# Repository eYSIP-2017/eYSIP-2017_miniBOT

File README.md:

# eYSIP-2017_miniBOT
A miniBot is designed and developed. Add necessary functions in Firebird-Blockly

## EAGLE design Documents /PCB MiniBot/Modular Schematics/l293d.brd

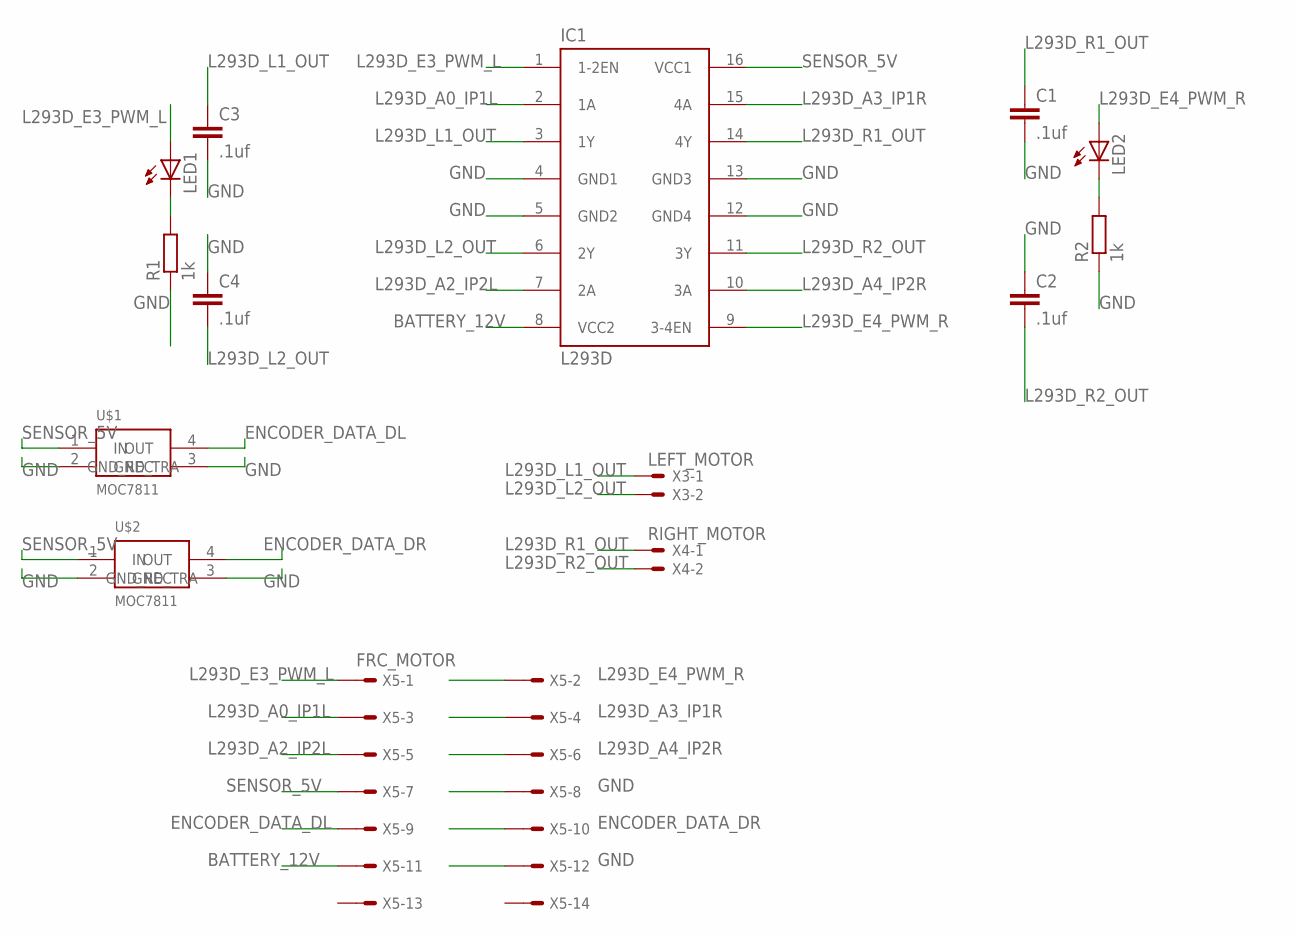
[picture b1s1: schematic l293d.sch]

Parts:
C1, C2, C3, C4: .1uf; C1206
IC1: L293D; DIL16
LED1, LED2: LEDSMT1206; 1206
R1, R2: 1k; M1206
U$1, U$2: MOC7811; THROUGH_HOLE_NORMAL
X3: LEFT_MOTOR; 22-23-2021
X4: RIGHT_MOTOR; 22-23-2021
X5: FRC_MOTOR; 057-014-1

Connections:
BATTERY_12V: IC1.8 (VCC2), X5.11
ENCODER_DATA_DL: U$1.4 (OUT), X5.9
ENCODER_DATA_DR: U$2.4 (OUT), X5.10
GND: C1.2, C2.1, C3.2, C4.1, IC1.4 (GND1), IC1.5 (GND2), IC1.12 (GND4), IC1.13 (GND3), R1.1, R2.1, U$1.2 (GND_TRA), U$1.3 (GND_REC), U$2.2 (GND_TRA), U$2.3 (GND_REC), X5.8, X5.12
L293D_A0_IP1L: IC1.2 (1A), X5.3
L293D_A2_IP2L: IC1.7 (2A), X5.5
L293D_A3_IP1R: IC1.15 (4A), X5.4
L293D_A4_IP2R: IC1.10 (3A), X5.6
L293D_E3_PWM_L: IC1.1 (1-2EN), LED1.A, X5.1
L293D_E4_PWM_R: IC1.9 (3-4EN), LED2.A, X5.2
L293D_L1_OUT: C3.1, IC1.3 (1Y), X3.1
L293D_L2_OUT: C4.2, IC1.6 (2Y), X3.2
L293D_R1_OUT: C1.1, IC1.14 (4Y), X4.1
L293D_R2_OUT: C2.2, IC1.11 (3Y), X4.2
unnamed: LED1.C, R1.2
unnamed: LED2.C, R2.2
SENSOR_5V: IC1.16 (VCC1), U$1.1 (IN), U$2.1 (IN), X5.7

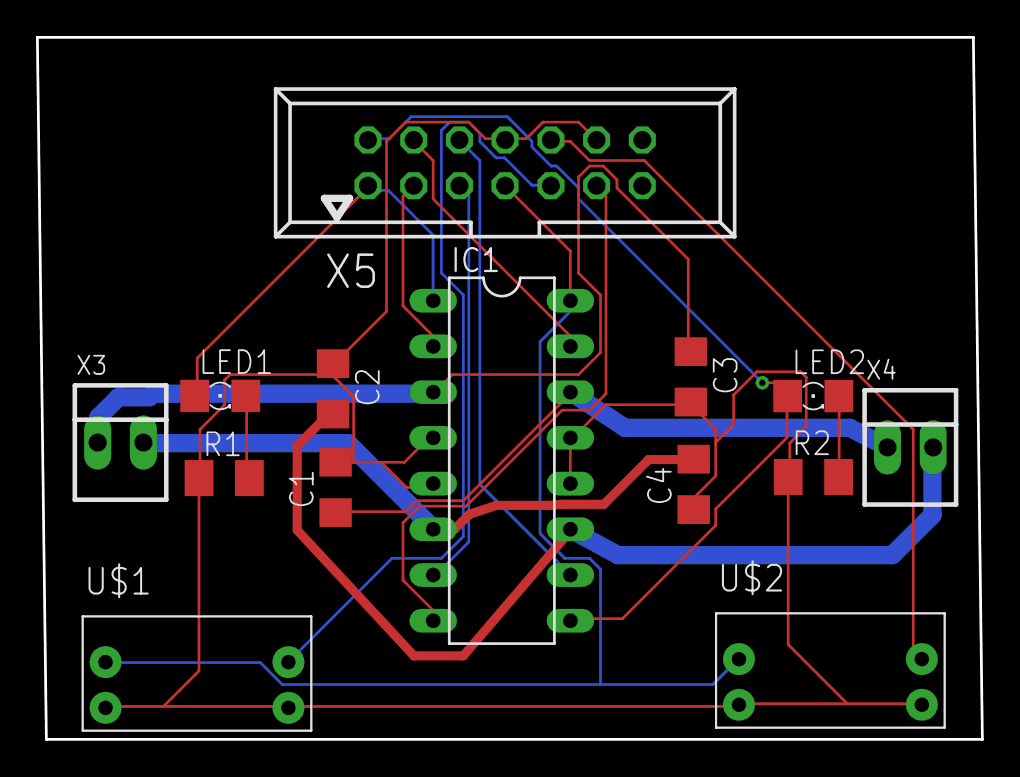
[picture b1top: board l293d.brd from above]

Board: 2 copper layers, 52.5 x 39.0 mm, 14 parts (0 on the bottom side), 17 nets.

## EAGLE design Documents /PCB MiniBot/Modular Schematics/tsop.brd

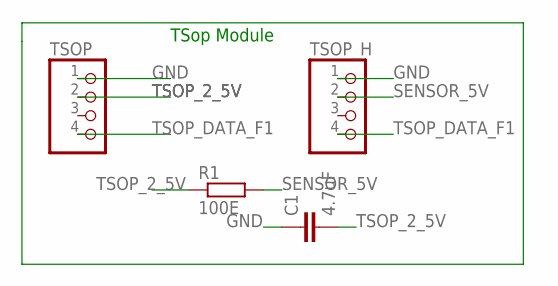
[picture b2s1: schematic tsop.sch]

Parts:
C1: 4.7uF; C1206
R1: 100E; R1206
TSOP: PINHD-1X4; 1X04
TSOP_H: PINHD-1X4; 1X04

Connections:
GND: C1.1, TSOP.1, TSOP_H.1
SENSOR_5V: R1.2, TSOP_H.2
TSOP_2_5V: C1.2, R1.1, TSOP.2
TSOP_DATA_F1: TSOP.4, TSOP_H.4

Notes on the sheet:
TSop Module

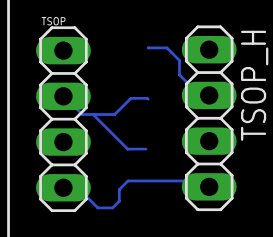
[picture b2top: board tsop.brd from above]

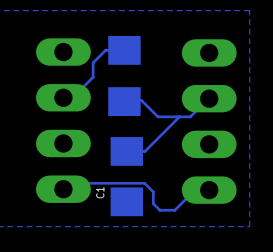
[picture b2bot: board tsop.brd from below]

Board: 2 copper layers, 4 parts (2 on the bottom side), 4 nets.

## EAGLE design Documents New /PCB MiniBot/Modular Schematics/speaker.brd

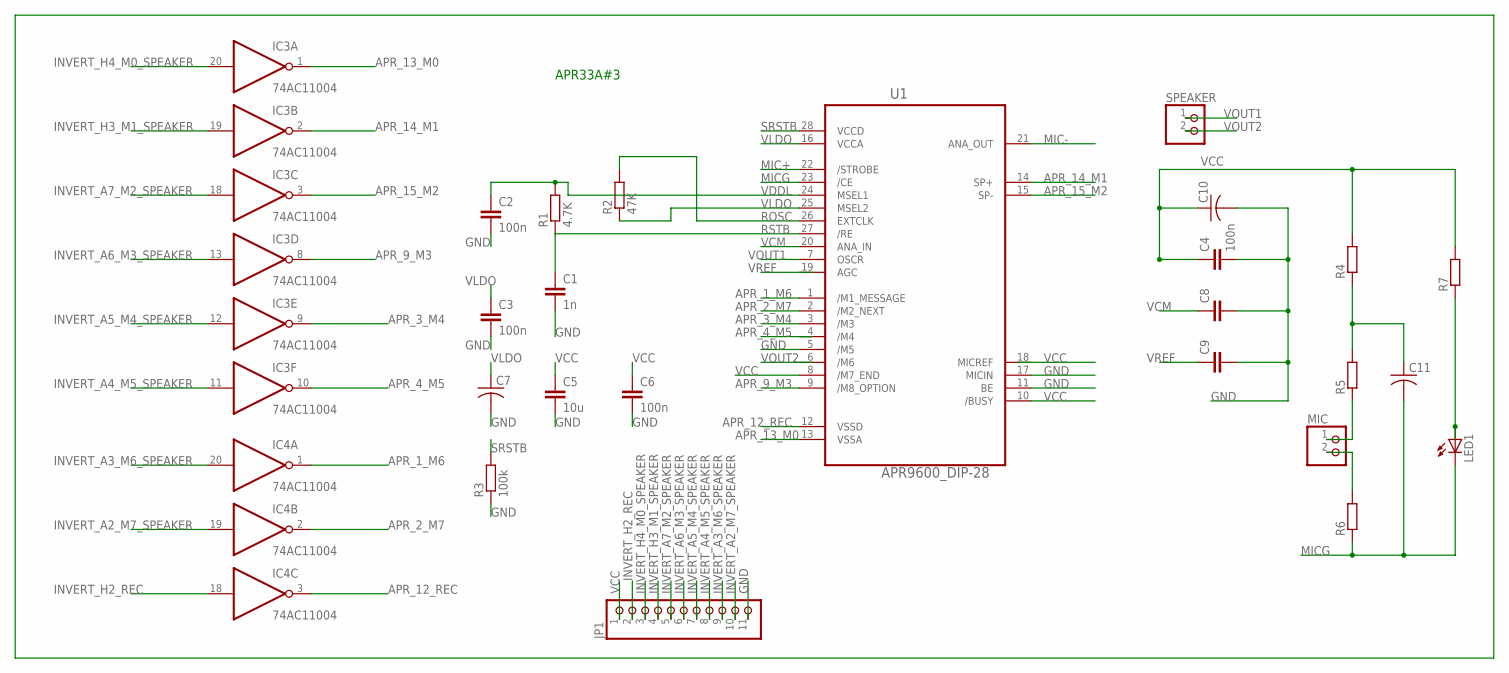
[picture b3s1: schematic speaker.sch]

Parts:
C1: 1n; C1206
C2, C3, C4, C6: 100n; C1206
C5: 10u; C1206
C7, C10, C11: C-US025-050X050; C025-050X050
C8, C9: C-EUC1206; C1206
IC3, IC4: 74AC11004; DIL20
JP1: PINHD-1X11; 1X11
LED1: LEDSMT1206; 1206
MIC: PINHD-1X2; 1X02
R1: 4.7K; M1206
R2: 47K; M1206
R3: 100k; M1206
R4, R5, R6, R7: R-EU_R1206; R1206
SPEAKER: PINHD-1X2; 1X02
U1: APR9600_DIP-28; DIP254P1525X550-28P

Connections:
APR_1_M6: IC4.1 (O), U1.1 (/M1_MESSAGE)
APR_2_M7: IC4.2 (O), U1.2 (/M2_NEXT)
APR_3_M4: IC3.9 (O), U1.3 (/M3)
APR_4_M5: IC3.10 (O)
APR_9_M3: IC3.8 (O), U1.9 (/M8_OPTION)
APR_12_REC: IC4.3 (O), U1.12 (VSSD)
APR_13_M0: IC3.1 (O), U1.13 (VSSA)
APR_14_M1: IC3.2 (O), U1.14 (SP+)
APR_15_M2: IC3.3 (O), U1.15 (SP-)
GND: C1.2, C2.2, C3.2, C4.2, C5.2, C6.2, C7.2, C8.2, C9.2, C10.2, IC3.4 (GND), IC3.5 (GND), IC3.6 (GND), IC3.7 (GND), IC4.4 (GND), IC4.5 (GND), IC4.6 (GND), IC4.7 (GND), JP1.11, R3.1, U1.5 (/M5), U1.11 (BE), U1.17 (MICIN)
INVERT_A2_M7_SPEAKER: IC4.19 (I), JP1.10
INVERT_A3_M6_SPEAKER: IC4.20 (I), JP1.9
INVERT_A4_M5_SPEAKER: IC3.11 (I), JP1.8
INVERT_A5_M4_SPEAKER: IC3.12 (I), JP1.7
INVERT_A6_M3_SPEAKER: IC3.13 (I), JP1.6
INVERT_A7_M2_SPEAKER: IC3.18 (I), JP1.5
INVERT_H3_M1_SPEAKER: IC3.19 (I), JP1.4
INVERT_H4_M0_SPEAKER: IC3.20 (I), JP1.3
INVERT_H4_REC: IC4.18 (I), JP1.2
MIC+: U1.22 (/STROBE)
MIC-: U1.21 (ANA_OUT)
MICG: C11.2, LED1.C, R6.1, U1.23 (/CE)
unnamed: C11.1, R4.1, R5.2
unnamed: MIC.1, R5.1
unnamed: MIC.2, R6.2
unnamed: LED1.A, R7.1
ROSC: R2.2, U1.26 (EXTCLK)
RSTB: C1.1, R1.1, U1.27 (/RE)
SRSTB: R3.2, U1.28 (VCCD)
VCC: C4.1, C5.1, C6.1, C10.1, IC3.15 (VCC), IC3.16 (VCC), IC4.15 (VCC), IC4.16 (VCC), JP1.1, R4.2, R7.2, U1.8 (/M7_END), U1.10 (/BUSY)
VCM: C8.1, U1.20 (ANA_IN)
VDDL: C2.1, R1.2, U1.24 (MSEL1)
VLDO: C3.1, C7.1, R2.1, U1.16 (VCCA), U1.25 (MSEL2)
VOUT1: SPEAKER.1, U1.7 (OSCR)
VOUT2: SPEAKER.2
VREF: C9.1

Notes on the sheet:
APR33A#3

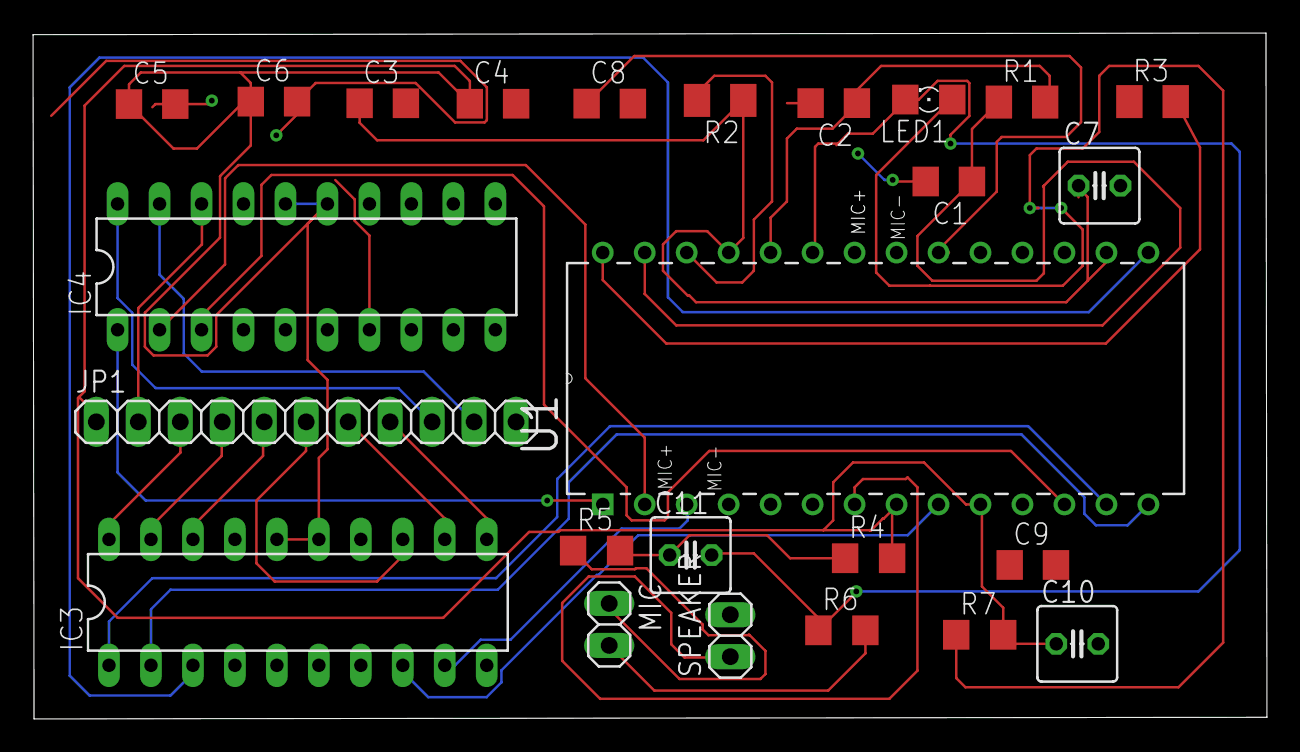
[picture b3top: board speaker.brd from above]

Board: 2 copper layers, 74.7 x 41.5 mm, 25 parts (0 on the bottom side), 31 nets.

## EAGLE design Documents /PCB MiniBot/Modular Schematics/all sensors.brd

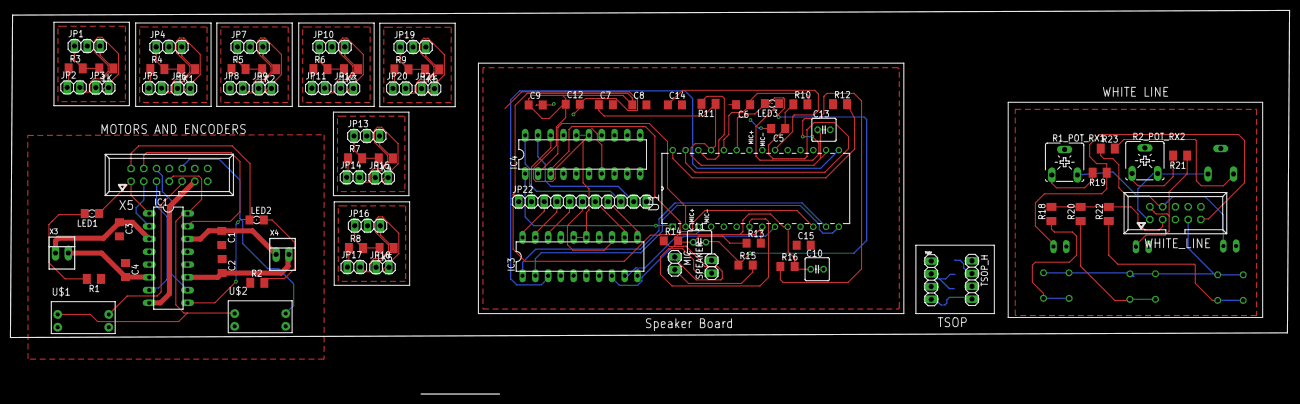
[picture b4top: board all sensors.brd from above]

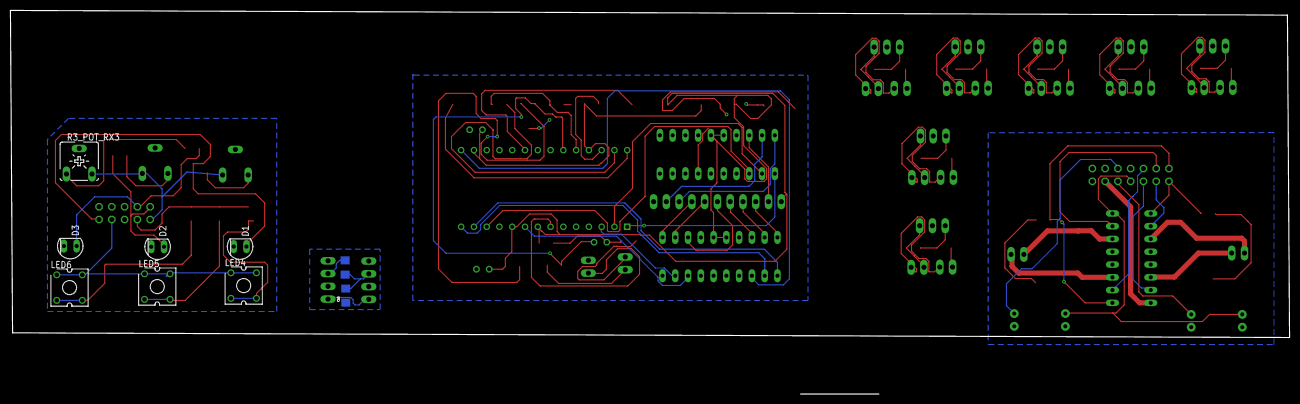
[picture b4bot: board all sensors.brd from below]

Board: 2 copper layers, 254.4 x 76.3 mm, 94 parts (9 on the bottom side), 93 nets.

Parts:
1K, 1K1, 1K2, 1K3, 1K4, 1K5, 1K6: 1k; M1206
C1, C2, C3, C4: .1uf; C1206
C5: 1n; C1206
C6, C7, C8, C12: 100n; C1206
C9: 10u; C1206
C10, C11, C13: C025-050X050
C14, C15: C1206
C16: 4.7uF; C1206
D1, D2, D3: SFH206
IC1: L293D; DIL16
IC3, IC4: 74AC11004; DIL20
JP1, JP4, JP7, JP10, JP13, JP16, JP19: 1X03
JP2, JP3, JP5, JP6, JP8, JP9, JP11, JP12, JP14, JP15, JP17, JP18, JP20, JP21: 1X02
JP22: 1X11
LED1, LED2, LED3: 1206
LED4, LED5, LED6: CP41B
MIC: 1X02
R1, R2, R3, R4, R5, R6, R7, R8, R9: 1k; M1206
R1_POT_RX1, R2_POT_RX2, R3_POT_RX3: CA6V
R10: 4.7K; M1206
R11: 47K; M1206
R12: 100k; M1206
R13, R14, R15, R16: R1206
R17: 100E; R1206
R18, R19, R20, R21, R22, R23: M1206
SPEAKER: 1X02
TSOP: 1X04
TSOP_H: 1X04
U1: APR9600_DIP-28; DIP254P1525X550-28P
U$1, U$2: MOC7811; THROUGH_HOLE_NORMAL
WHITE_LINE: 057-010-1
X3: LEFT_MOTOR; 22-23-2021
X4: RIGHT_MOTOR; 22-23-2021
X5: FRC_MOTOR; 057-014-1

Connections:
3.3V: R18.2, R20.2, R22.2, WHITE_LINE.3
5V: R1_POT_RX1.E, R2_POT_RX2.E, R3_POT_RX3.E, WHITE_LINE.1
APR_1_M6: IC4.1, U1.1
APR_2_M7: IC4.2, U1.2
APR_3_M4: IC3.9, U1.3
APR_9_M3: IC3.8, U1.9
APR_12_REC: IC4.3, U1.12
APR_13_M0: IC3.1, U1.13
APR_14_M1: IC3.2, U1.14
APR_15_M2: IC3.3, U1.15
BATTERY_12V: IC1.8, X5.11
ENCODER_DATA_DL: U$1.4, X5.9
ENCODER_DATA_DR: U$2.4, X5.10
GND: C1.2, C2.1, C3.2, C4.1, IC1.4, IC1.5, IC1.12, IC1.13, R1.1, R2.1, U$1.2, U$1.3, U$2.2, U$2.3, X5.8, X5.12
GND1: JP1.2, JP2.2, JP3.2
GND2: JP4.2, JP5.2, JP6.2
GND3: JP7.2, JP8.2, JP9.2
GND4: JP10.2, JP11.2, JP12.2
GND5: JP13.2, JP14.2, JP15.2
GND6: JP16.2, JP17.2, JP18.2
GND7: JP19.2, JP20.2, JP21.2
GND8: C5.2, C6.2, C7.2, C8.2, C9.2, C10.2, C12.2, C13.2, C14.2, C15.2, IC3.4, IC3.5, IC3.6, IC3.7, IC4.4, IC4.5, IC4.6, IC4.7, JP22.11, R12.1, U1.5, U1.11, U1.17
GND9: C16.1, TSOP.1, TSOP_H.1
GND10: D1.K, D2.K, D3.K, WHITE_LINE.5
INVERT_A2_M7_SPEAKER: IC4.19, JP22.10
INVERT_A3_M6_SPEAKER: IC4.20, JP22.9
INVERT_A4_M5_SPEAKER: IC3.11, JP22.8
INVERT_A5_M4_SPEAKER: IC3.12, JP22.7
INVERT_A6_M3_SPEAKER: IC3.13, JP22.6
INVERT_A7_M2_SPEAKER: IC3.18, JP22.5
INVERT_H3_M1_SPEAKER: IC3.19, JP22.4
INVERT_H4_M0_SPEAKER: IC3.20, JP22.3
INVERT_H4_REC: IC4.18, JP22.2
L293D_A0_IP1L: IC1.2, X5.3
L293D_A2_IP2L: IC1.7, X5.5
L293D_A3_IP1R: IC1.15, X5.4
L293D_A4_IP2R: IC1.10, X5.6
L293D_E3_PWM_L: IC1.1, LED1.A, X5.1
L293D_E4_PWM_R: IC1.9, LED2.A, X5.2
L293D_L1_OUT: C3.1, IC1.3, X3.1
L293D_L2_OUT: C4.2, IC1.6, X3.2
L293D_R1_OUT: C1.1, IC1.14, X4.1
L293D_R2_OUT: C2.2, IC1.11, X4.2
MICG: C11.2, LED3.C, R15.1, U1.23
unnamed: JP5.1, R4.1
unnamed: LED1.C, R1.2
unnamed: JP8.1, R5.1
unnamed: LED2.C, R2.2
unnamed: JP11.1, R6.1
unnamed: JP14.1, R7.1
unnamed: JP17.1, R8.1
unnamed: JP20.1, R9.1
unnamed: JP2.1, R3.1
unnamed: C11.1, R13.1, R14.2
unnamed: MIC.1, R14.1
unnamed: MIC.2, R15.2
unnamed: LED3.A, R16.1
unnamed: R1_POT_RX1.A, R19.2
unnamed: R2_POT_RX2.A, R21.2
unnamed: R3_POT_RX3.A, R23.2
unnamed: LED6.2, LED6.3, R22.1
unnamed: LED4.2, LED4.3, R18.1
unnamed: LED5.2, LED5.3, R20.1
PIN_DATA: 1K.1, JP1.3, JP3.1
PIN_DATA1: 1K1.1, JP4.3, JP6.1
PIN_DATA2: 1K2.1, JP7.3, JP9.1
PIN_DATA3: 1K3.1, JP10.3, JP12.1
PIN_DATA4: 1K4.1, JP13.3, JP15.1
PIN_DATA5: 1K5.1, JP16.3, JP18.1
PIN_DATA6: 1K6.1, JP19.3, JP21.1
PIN_DATA_A1: LED4.1, LED4.4, LED5.1, LED5.4, LED6.1, LED6.4, WHITE_LINE.7
PIN_DATA_K0: D1.A, R19.1, WHITE_LINE.9
PIN_DATA_K1: D2.A, R21.1, WHITE_LINE.2
PIN_DATA_K2: D3.A, R23.1, WHITE_LINE.4
ROSC: R11.2, U1.26
RSTB: C5.1, R10.1, U1.27
SENSOR_5V: IC1.16, U$1.1, U$2.1, X5.7
SENSOR_5V1: 1K.2, JP1.1, R3.2
SENSOR_5V2: 1K1.2, JP4.1, R4.2
SENSOR_5V3: 1K2.2, JP7.1, R5.2
SENSOR_5V4: 1K3.2, JP10.1, R6.2
SENSOR_5V5: 1K4.2, JP13.1, R7.2
SENSOR_5V6: 1K5.2, JP16.1, R8.2
SENSOR_5V7: 1K6.2, JP19.1, R9.2
SENSOR_5V8: R17.2, TSOP_H.2
SRSTB: R12.2, U1.28
TSOP_2_5V: C16.2, R17.1, TSOP.2
TSOP_DATA_F1: TSOP.4, TSOP_H.4
VCC: C8.1, C9.1, C10.1, C12.1, IC3.15, IC3.16, IC4.15, IC4.16, JP22.1, R13.2, R16.2, U1.8, U1.10
VCM: C14.1, U1.20
VDDL: C6.1, R10.2, U1.24
VLDO: C7.1, C13.1, R11.1, U1.16, U1.25
VOUT1: SPEAKER.1, U1.7

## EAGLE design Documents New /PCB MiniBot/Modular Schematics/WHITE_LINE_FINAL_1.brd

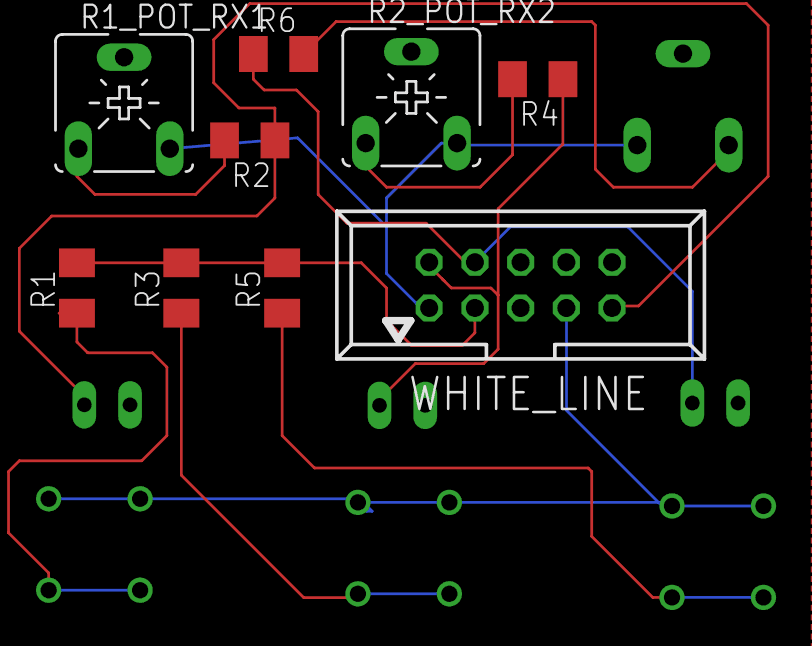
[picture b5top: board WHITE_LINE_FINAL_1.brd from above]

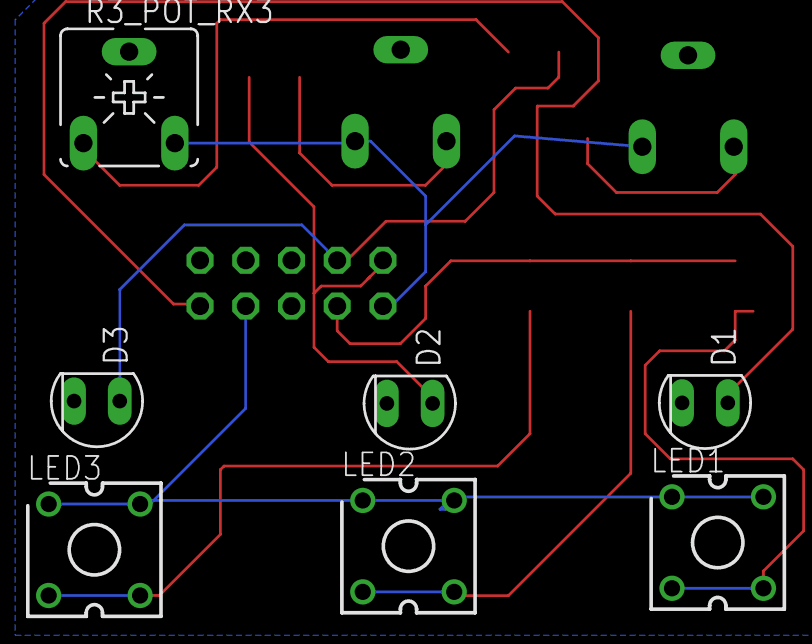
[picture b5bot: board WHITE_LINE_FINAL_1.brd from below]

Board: 2 copper layers, 16 parts (7 on the bottom side), 13 nets.

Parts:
D1, D2, D3: SFH206
LED1, LED2, LED3: CP41B
R1, R2, R3, R4, R5, R6: M1206
R1_POT_RX1, R2_POT_RX2, R3_POT_RX3: CA6V
WHITE_LINE: 057-010-1

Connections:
3.3V: R1.2, R3.2, R5.2, WHITE_LINE.3
5V: R1_POT_RX1.E, R2_POT_RX2.E, R3_POT_RX3.E, WHITE_LINE.1
GND: D1.K, D2.K, D3.K, WHITE_LINE.5
unnamed: R1_POT_RX1.A, R2.2
unnamed: LED2.2, LED2.3, R3.1
unnamed: R2_POT_RX2.A, R4.2
unnamed: R3_POT_RX3.A, R6.2
unnamed: LED3.2, LED3.3, R5.1
unnamed: LED1.2, LED1.3, R1.1
PIN_DATA_A1: LED1.1, LED1.4, LED2.1, LED2.4, LED3.1, LED3.4, WHITE_LINE.7
PIN_DATA_K0: D1.A, R2.1, WHITE_LINE.9
PIN_DATA_K1: D2.A, R4.1, WHITE_LINE.2
PIN_DATA_K2: D3.A, R6.1, WHITE_LINE.4

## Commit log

2017-07-09 blockly3
2017-07-10 changes in servo and zigbee
2017-07-10 check
2017-07-14 Report
2017-07-14 del1
2017-07-14 del2
2017-07-14 del3
2017-07-14 del4
2017-07-14 del5
2017-07-14 Xbee Blutooth and Servo Code
2017-07-14 ReportMiniBOT
2017-07-15 Documentation new
2017-07-15 Documentation updated
2017-07-19 Removed unnecessary files
2017-07-19 removed file
2017-07-19 removed
2017-07-19 Updated Bwith new Blocks
2017-07-19 Xbee,Bluetooth and Servo
2017-07-19 Documentation
2017-07-19 Reort MiniBOT
2017-07-19 Report MiniBOT
2017-07-20 changes inloop
2017-07-20 added blockly code

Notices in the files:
parts and their libraries:
aplus: Created by SCRIPT exported from Ultra Librarian Gold 5.3.88 Copyright © 1999-2010
aplus: Created by Ultra Librarian Gold 5.3.88 Copyright © 1999-2010
